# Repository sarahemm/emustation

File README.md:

# emustation
Modular cyberdeck project

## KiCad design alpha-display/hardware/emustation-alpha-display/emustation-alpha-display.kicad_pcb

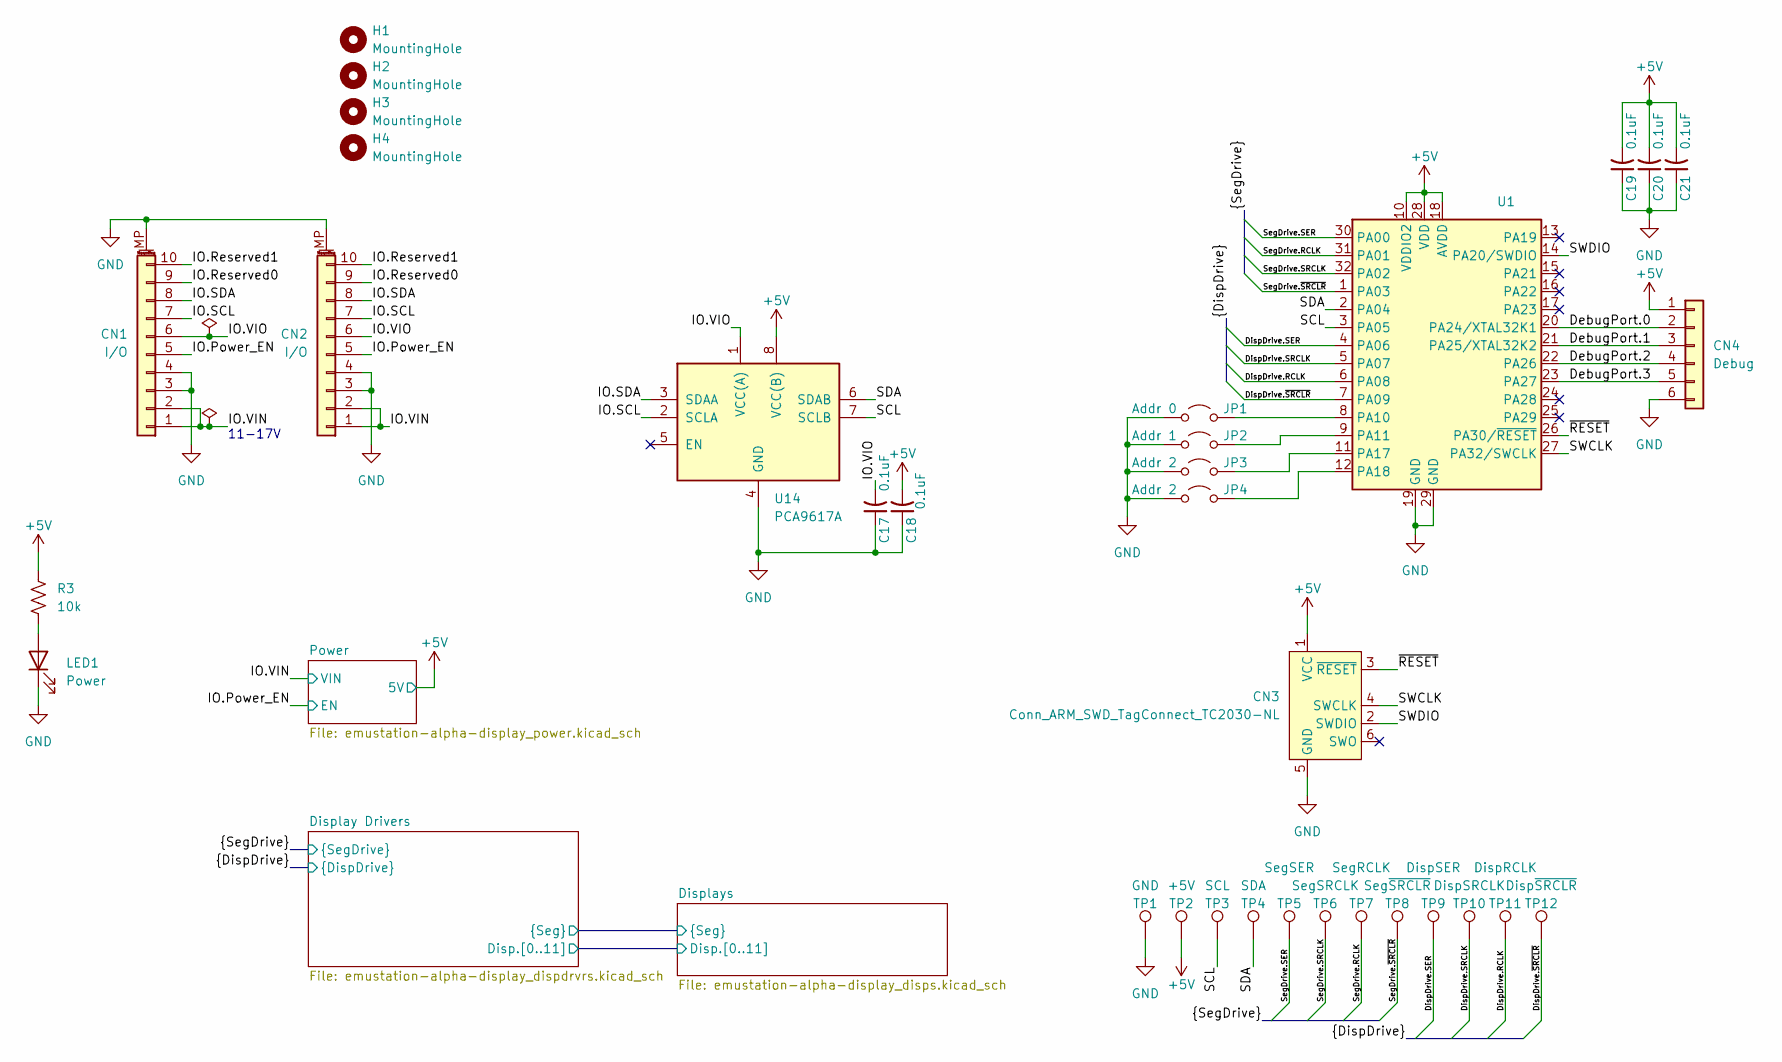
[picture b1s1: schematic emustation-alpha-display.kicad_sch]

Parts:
C17, C18, C19, C20, C21: 0.1uF; C_0603_1608Metric
CN1, CN2: I/O; CF4210FH0R0-05-NH_1x10-1MP_P0.50mm_Horizontal
CN3: Conn_ARM_SWD_TagConnect_TC2030-NL; Tag-Connect_TC2030-IDC-NL_2x03_P1.27mm_Vertical
CN4: Debug; PinHeader_2x03_P1.00mm_Vertical
H1, H2, H3, H4: MountingHole; MountingHole_3.2mm_M3
JP1: Addr 0; SolderJumper-2_P1.3mm_Open_TrianglePad1.0x1.5mm
JP2: Addr 1; SolderJumper-2_P1.3mm_Open_TrianglePad1.0x1.5mm
JP3, JP4: Addr 2; SolderJumper-2_P1.3mm_Open_TrianglePad1.0x1.5mm
LED1: Power; LED_1206_3216Metric
R3: 10k; R_0603_1608Metric
TP1: GND; TestPoint_THTPad_D2.0mm_Drill1.0mm
TP2: +5V; TestPoint_Pad_3.0x3.0mm
TP3: SCL; TestPoint_Pad_2.0x2.0mm
TP4: SDA; TestPoint_Pad_2.0x2.0mm
TP5: SegSER; TestPoint_Pad_2.0x2.0mm
TP6: SegSRCLK; TestPoint_Pad_2.0x2.0mm
TP7: SegRCLK; TestPoint_Pad_2.0x2.0mm
TP8: Seg~{SRCLR}; TestPoint_Pad_2.0x2.0mm
TP9: DispSER; TestPoint_Pad_1.0x1.0mm
TP10: DispSRCLK; TestPoint_Pad_1.0x1.0mm
TP11: DispRCLK; TestPoint_Pad_1.0x1.0mm
TP12: Disp~{SRCLR}; TestPoint_Pad_1.0x1.0mm
U1: TQFP-32_7x7mm_P0.8mm
U14: PCA9617A; TSSOP-8_3x3mm_P0.65mm

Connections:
+5V: C18.2, C19.2, C20.2, C21.2, CN3.1 (VCC), CN4.1, R3.1, TP2.1 (1_1), U1.10 (VDDIO2), U1.18 (AVDD), U1.28 (VDD), U14.8 (VCC(B)); also elsewhere on the board
/DebugPort.0: CN4.2, U1.20 (PA24/XTAL32K1)
/DebugPort.1: CN4.3, U1.21 (PA25/XTAL32K2)
/DebugPort.2: CN4.4, U1.22 (PA26)
/DebugPort.3: CN4.5, U1.23 (PA27)
/DispDrive.RCLK: TP11.1 (1_1), U1.6 (PA08); also elsewhere on the board
/DispDrive.SER: TP9.1 (1_1), U1.4 (PA06); also elsewhere on the board
/DispDrive.SRCLK: TP10.1 (1_1), U1.5 (PA07); also elsewhere on the board
/DispDrive.~SRCLR: TP12.1 (1_1), U1.7 (PA09); also elsewhere on the board
/IO.Power_EN: CN1.5, CN2.5; also elsewhere on the board
/IO.Reserved0: CN1.9, CN2.9
/IO.Reserved1: CN1.10, CN2.10
/IO.SCL: CN1.7, CN2.7, U14.2 (SCLA)
/IO.SDA: CN1.8, CN2.8, U14.3 (SDAA)
/IO.VIN: CN1.1, CN1.2, CN2.1, CN2.2; also elsewhere on the board
/IO.VIO: C17.2, CN1.6, CN2.6, U14.1 (VCC(A))
/SCL: TP3.1 (1_1), U1.3 (PA05), U14.7 (SCLB)
/SDA: TP4.1 (1_1), U1.2 (PA04), U14.6 (SDAB)
/SWCLK: CN3.4 (SWCLK), U1.27 (PA32/SWCLK)
/SWDIO: CN3.2 (SWDIO), U1.14 (PA20/SWDIO)
/SegDrive.RCLK: TP7.1 (1_1), U1.31 (PA01); also elsewhere on the board
/SegDrive.SER: TP5.1 (1_1), U1.30 (PA00); also elsewhere on the board
/SegDrive.SRCLK: TP6.1 (1_1), U1.32 (PA02); also elsewhere on the board
/SegDrive.~SRCLR: TP8.1 (1_1), U1.1 (PA03); also elsewhere on the board
/~RESET: CN3.3 (~RESET), U1.26 (PA30/~RESET)
GND: C17.1, C18.1, C19.1, C20.1, C21.1, CN1.3, CN1.4, CN1.MP (MountPin), CN2.3, CN2.4, CN2.MP (MountPin), CN3.5 (GND), CN4.6, JP1.1 (A), JP2.1 (A), JP3.1 (A), JP4.1 (A), LED1.1 (K), TP1.1 (1_1), U1.19 (GND), U1.29 (GND), U14.4 (GND); also elsewhere on the board
unnamed: JP1.2 (B), U1.8 (PA10)
unnamed: JP2.2 (B), U1.9 (PA11)
unnamed: JP3.2 (B), U1.11 (PA17)
unnamed: JP4.2 (B), U1.12 (PA18)
unnamed: LED1.2 (A), R3.2

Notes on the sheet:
11-17V

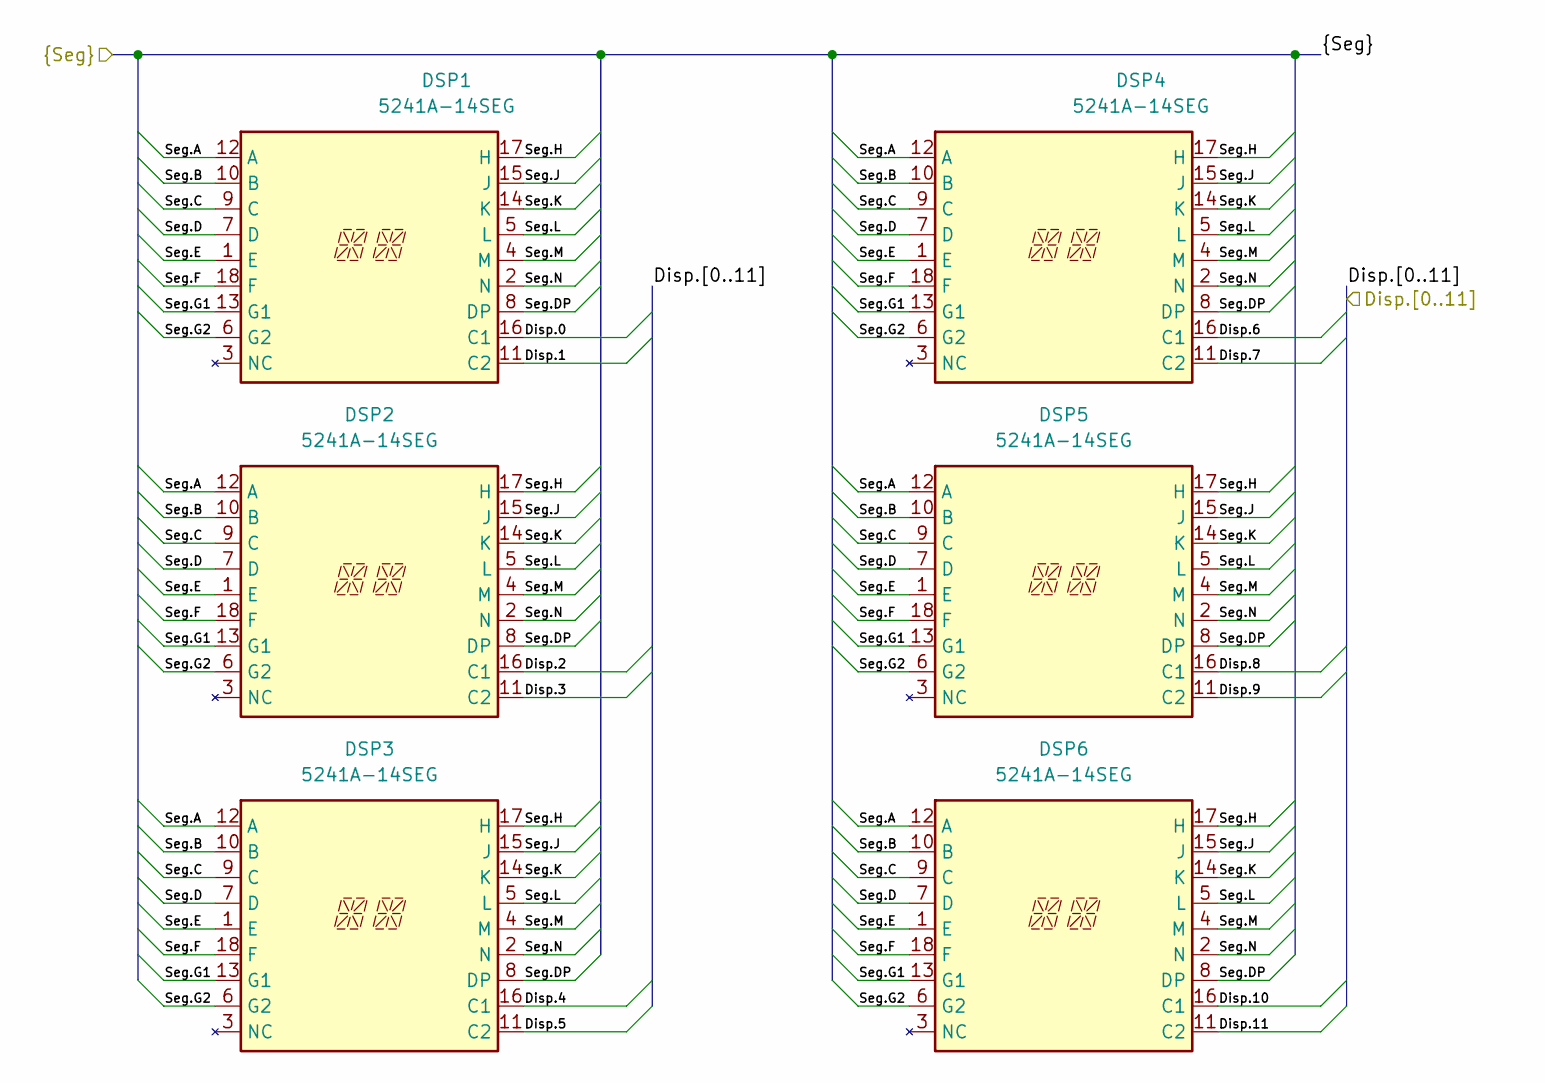
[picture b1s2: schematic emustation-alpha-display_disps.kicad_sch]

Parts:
DSP1, DSP2, DSP3, DSP4, DSP5, DSP6: 5241A-14SEG

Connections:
/Display Drivers/Disp.0: DSP1.16 (C1); also elsewhere on the board
/Display Drivers/Disp.1: DSP1.11 (C2); also elsewhere on the board
/Display Drivers/Disp.2: DSP2.16 (C1); also elsewhere on the board
/Display Drivers/Disp.3: DSP2.11 (C2); also elsewhere on the board
/Display Drivers/Disp.4: DSP3.16 (C1); also elsewhere on the board
/Display Drivers/Disp.5: DSP3.11 (C2); also elsewhere on the board
/Display Drivers/Disp.6: DSP4.16 (C1); also elsewhere on the board
/Display Drivers/Disp.7: DSP4.11 (C2); also elsewhere on the board
/Display Drivers/Disp.8: DSP5.16 (C1); also elsewhere on the board
/Display Drivers/Disp.9: DSP5.11 (C2); also elsewhere on the board
/Display Drivers/Disp.10: DSP6.16 (C1); also elsewhere on the board
/Display Drivers/Disp.11: DSP6.11 (C2); also elsewhere on the board
/Display Drivers/Seg.A: DSP1.12 (A), DSP2.12 (A), DSP3.12 (A), DSP4.12 (A), DSP5.12 (A), DSP6.12 (A); also elsewhere on the board
/Display Drivers/Seg.B: DSP1.10 (B), DSP2.10 (B), DSP3.10 (B), DSP4.10 (B), DSP5.10 (B), DSP6.10 (B); also elsewhere on the board
/Display Drivers/Seg.C: DSP1.9 (C), DSP2.9 (C), DSP3.9 (C), DSP4.9 (C), DSP5.9 (C), DSP6.9 (C); also elsewhere on the board
/Display Drivers/Seg.D: DSP1.7 (D), DSP2.7 (D), DSP3.7 (D), DSP4.7 (D), DSP5.7 (D), DSP6.7 (D); also elsewhere on the board
/Display Drivers/Seg.DP: DSP1.8 (DP), DSP2.8 (DP), DSP3.8 (DP), DSP4.8 (DP), DSP5.8 (DP), DSP6.8 (DP); also elsewhere on the board
/Display Drivers/Seg.E: DSP1.1 (E), DSP2.1 (E), DSP3.1 (E), DSP4.1 (E), DSP5.1 (E), DSP6.1 (E); also elsewhere on the board
/Display Drivers/Seg.F: DSP1.18 (F), DSP2.18 (F), DSP3.18 (F), DSP4.18 (F), DSP5.18 (F), DSP6.18 (F); also elsewhere on the board
/Display Drivers/Seg.G1: DSP1.13 (G1), DSP2.13 (G1), DSP3.13 (G1), DSP4.13 (G1), DSP5.13 (G1), DSP6.13 (G1); also elsewhere on the board
/Display Drivers/Seg.G2: DSP1.6 (G2), DSP2.6 (G2), DSP3.6 (G2), DSP4.6 (G2), DSP5.6 (G2), DSP6.6 (G2); also elsewhere on the board
/Display Drivers/Seg.H: DSP1.17 (H), DSP2.17 (H), DSP3.17 (H), DSP4.17 (H), DSP5.17 (H), DSP6.17 (H); also elsewhere on the board
/Display Drivers/Seg.J: DSP1.15 (J), DSP2.15 (J), DSP3.15 (J), DSP4.15 (J), DSP5.15 (J), DSP6.15 (J); also elsewhere on the board
/Display Drivers/Seg.K: DSP1.14 (K), DSP2.14 (K), DSP3.14 (K), DSP4.14 (K), DSP5.14 (K), DSP6.14 (K); also elsewhere on the board
/Display Drivers/Seg.L: DSP1.5 (L), DSP2.5 (L), DSP3.5 (L), DSP4.5 (L), DSP5.5 (L), DSP6.5 (L); also elsewhere on the board
/Display Drivers/Seg.M: DSP1.4 (M), DSP2.4 (M), DSP3.4 (M), DSP4.4 (M), DSP5.4 (M), DSP6.4 (M); also elsewhere on the board
/Display Drivers/Seg.N: DSP1.2 (N), DSP2.2 (N), DSP3.2 (N), DSP4.2 (N), DSP5.2 (N), DSP6.2 (N); also elsewhere on the board

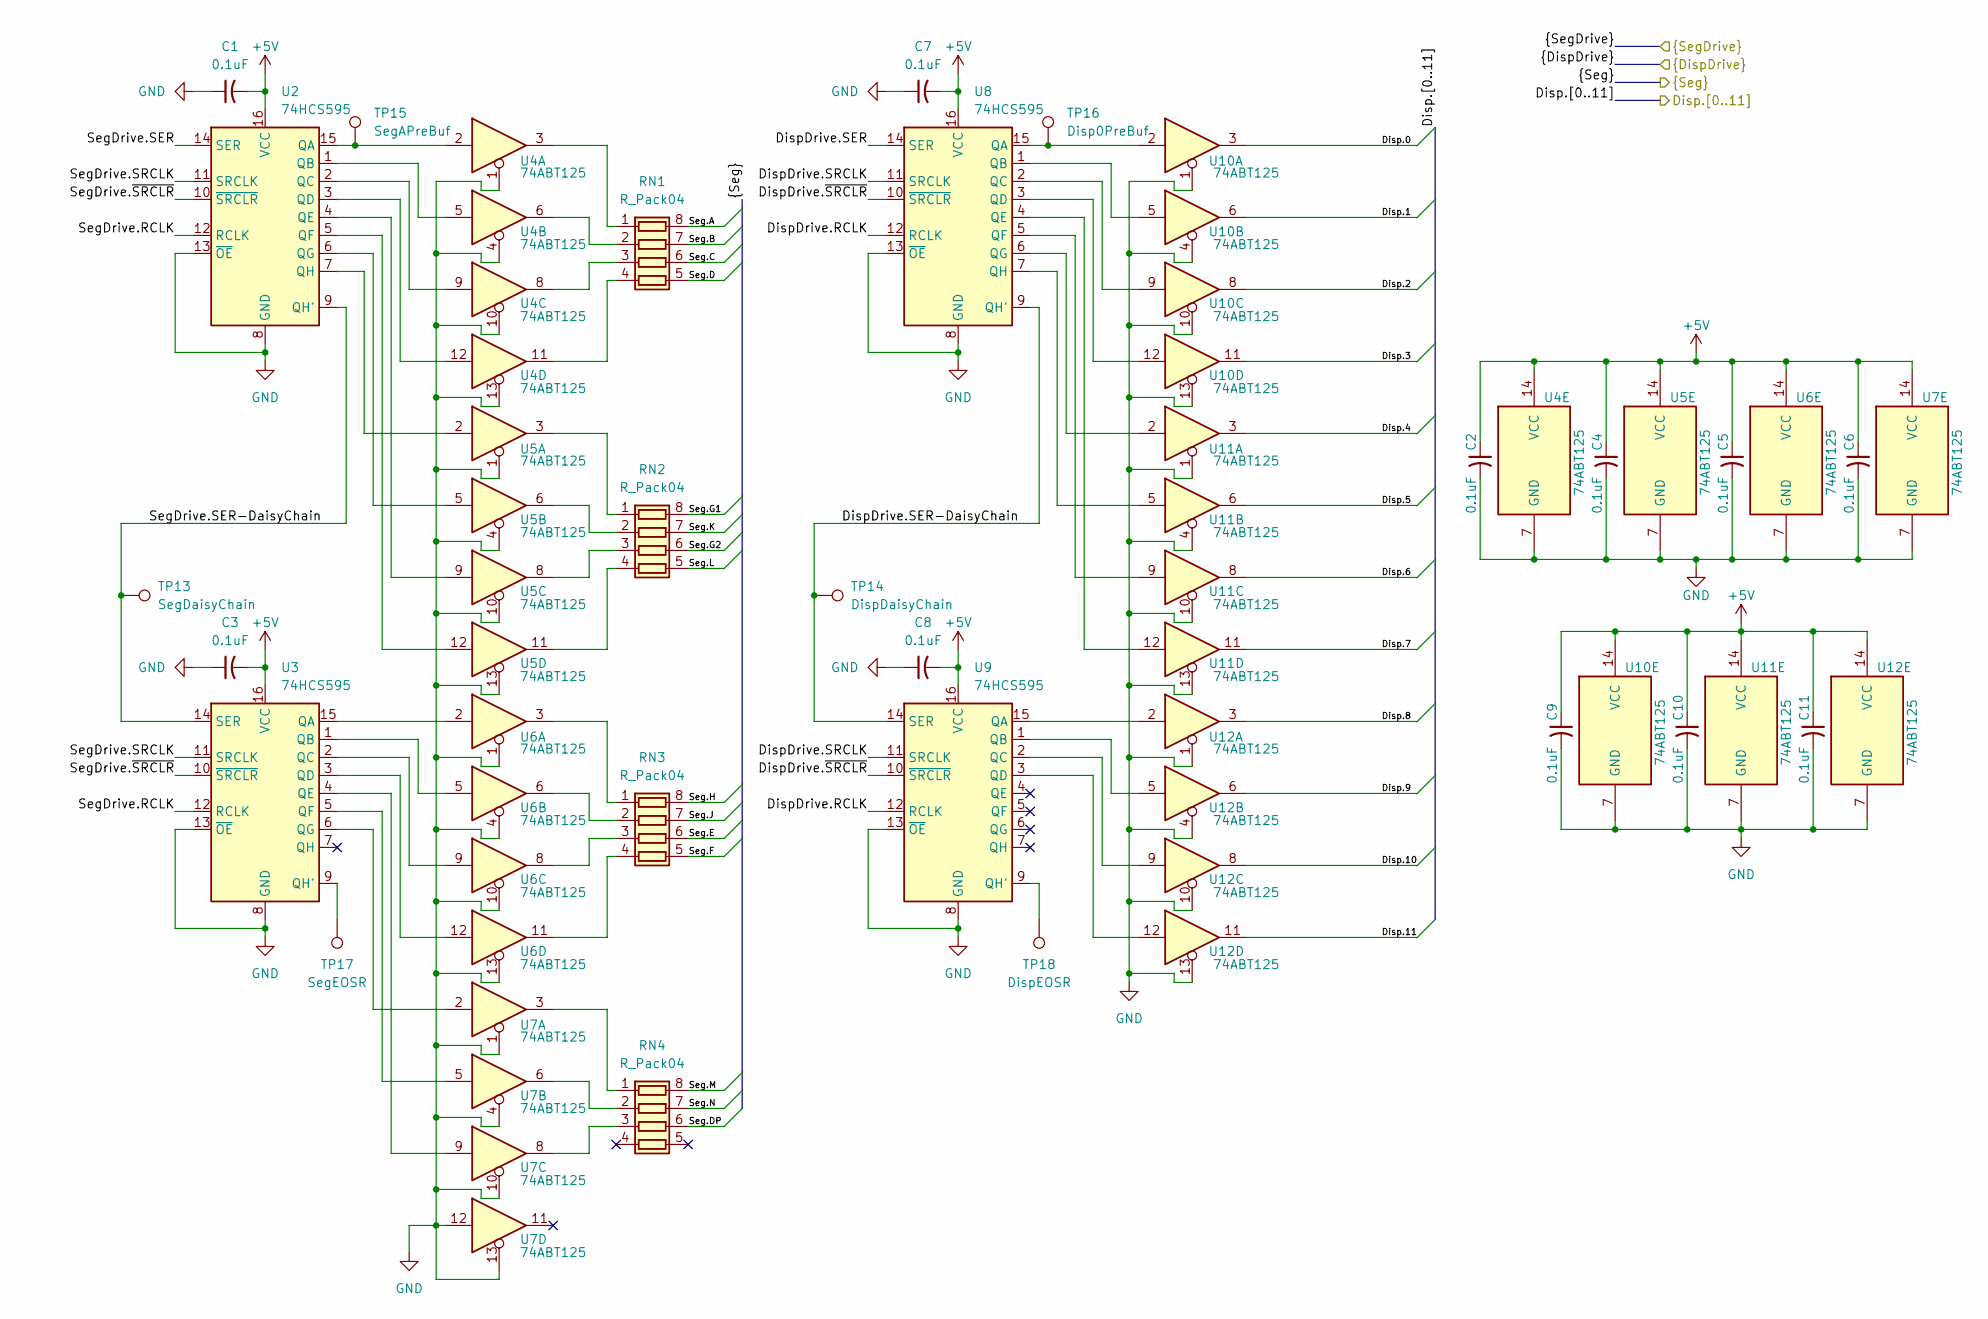
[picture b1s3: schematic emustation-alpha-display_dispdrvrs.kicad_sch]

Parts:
C1, C2, C3, C4, C5, C6, C7, C8, C9, C10, C11: 0.1uF; C_0603_1608Metric
RN1, RN2, RN3, RN4: R_Pack04; R_Array_Convex_4x0603
TP13: SegDaisyChain; TestPoint_Pad_2.0x2.0mm
TP14: DispDaisyChain; TestPoint_Pad_2.0x2.0mm
TP15: SegAPreBuf; TestPoint_Pad_2.0x2.0mm
TP16: Disp0PreBuf; TestPoint_Pad_2.0x2.0mm
TP17: SegEOSR; TestPoint_Pad_2.0x2.0mm
TP18: DispEOSR; TestPoint_Pad_2.0x2.0mm
U2, U3, U8, U9: 74HCS595; TSSOP-16_4.4x5mm_P0.65mm
U4, U5, U6, U7, U10, U11, U12: 74ABT125; TSSOP-14_4.4x5mm_P0.65mm

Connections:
+5V: C1.2, C2.1, C3.2, C4.1, C5.1, C6.1, C7.2, C8.2, C9.1, C10.1, C11.1, U2.16 (VCC), U3.16 (VCC), U4.14 (VCC), U5.14 (VCC), U6.14 (VCC), U7.14 (VCC), U8.16 (VCC), U9.16 (VCC), U10.14 (VCC), U11.14 (VCC), U12.14 (VCC); also elsewhere on the board
/DispDrive.RCLK: U8.12 (RCLK), U9.12 (RCLK); also elsewhere on the board
/DispDrive.SER: U8.14 (SER); also elsewhere on the board
/DispDrive.SRCLK: U8.11 (SRCLK), U9.11 (SRCLK); also elsewhere on the board
/DispDrive.~SRCLR: U8.10 (~SRCLR), U9.10 (~SRCLR); also elsewhere on the board
/Display Drivers/Disp.0: U10.3; also elsewhere on the board
/Display Drivers/Disp.1: U10.6; also elsewhere on the board
/Display Drivers/Disp.2: U10.8; also elsewhere on the board
/Display Drivers/Disp.3: U10.11; also elsewhere on the board
/Display Drivers/Disp.4: U11.3; also elsewhere on the board
/Display Drivers/Disp.5: U11.6; also elsewhere on the board
/Display Drivers/Disp.6: U11.8; also elsewhere on the board
/Display Drivers/Disp.7: U11.11; also elsewhere on the board
/Display Drivers/Disp.8: U12.3; also elsewhere on the board
/Display Drivers/Disp.9: U12.6; also elsewhere on the board
/Display Drivers/Disp.10: U12.8; also elsewhere on the board
/Display Drivers/Disp.11: U12.11; also elsewhere on the board
/Display Drivers/DispDrive.SER-DaisyChain: TP14.1 (1_1), U8.9 (QH'), U9.14 (SER)
/Display Drivers/Seg.A: RN1.8 (R1.2); also elsewhere on the board
/Display Drivers/Seg.B: RN1.7 (R2.2); also elsewhere on the board
/Display Drivers/Seg.C: RN1.6 (R3.2); also elsewhere on the board
/Display Drivers/Seg.D: RN1.5 (R4.2); also elsewhere on the board
/Display Drivers/Seg.DP: RN4.6 (R3.2); also elsewhere on the board
/Display Drivers/Seg.E: RN3.6 (R3.2); also elsewhere on the board
/Display Drivers/Seg.F: RN3.5 (R4.2); also elsewhere on the board
/Display Drivers/Seg.G1: RN2.8 (R1.2); also elsewhere on the board
/Display Drivers/Seg.G2: RN2.6 (R3.2); also elsewhere on the board
/Display Drivers/Seg.H: RN3.8 (R1.2); also elsewhere on the board
/Display Drivers/Seg.J: RN3.7 (R2.2); also elsewhere on the board
/Display Drivers/Seg.K: RN2.7 (R2.2); also elsewhere on the board
/Display Drivers/Seg.L: RN2.5 (R4.2); also elsewhere on the board
/Display Drivers/Seg.M: RN4.8 (R1.2); also elsewhere on the board
/Display Drivers/Seg.N: RN4.7 (R2.2); also elsewhere on the board
/Display Drivers/SegDrive.SER-DaisyChain: TP13.1 (1_1), U2.9 (QH'), U3.14 (SER)
/SegDrive.RCLK: U2.12 (RCLK), U3.12 (RCLK); also elsewhere on the board
/SegDrive.SER: U2.14 (SER); also elsewhere on the board
/SegDrive.SRCLK: U2.11 (SRCLK), U3.11 (SRCLK); also elsewhere on the board
/SegDrive.~SRCLR: U2.10 (~SRCLR), U3.10 (~SRCLR); also elsewhere on the board
GND: C1.1, C2.2, C3.1, C4.2, C5.2, C6.2, C7.1, C8.1, C9.2, C10.2, C11.2, U2.8 (GND), U2.13 (~OE), U3.8 (GND), U3.13 (~OE), U4.1, U4.4, U4.7 (GND), U4.10, U4.13, U5.1, U5.4, U5.7 (GND), U5.10, U5.13, U6.1, U6.4, U6.7 (GND), U6.10, U6.13, U7.1, U7.4, U7.7 (GND), U7.10, U7.12, U7.13, U8.8 (GND), U8.13 (~OE), U9.8 (GND), U9.13 (~OE), U10.1, U10.4, U10.7 (GND), U10.10, U10.13, U11.1, U11.4, U11.7 (GND), U11.10, U11.13, U12.1, U12.4, U12.7 (GND), U12.10, U12.13; also elsewhere on the board
unnamed: RN1.1 (R1.1), U4.3
unnamed: RN1.2 (R2.1), U4.6
unnamed: RN1.3 (R3.1), U4.8
unnamed: RN1.4 (R4.1), U4.11
unnamed: RN2.1 (R1.1), U5.3
unnamed: RN2.2 (R2.1), U5.6
unnamed: RN2.3 (R3.1), U5.8
unnamed: RN2.4 (R4.1), U5.11
unnamed: RN3.1 (R1.1), U6.3
unnamed: RN3.2 (R2.1), U6.6
unnamed: RN3.3 (R3.1), U6.8
unnamed: RN3.4 (R4.1), U6.11
unnamed: RN4.1 (R1.1), U7.3
unnamed: RN4.2 (R2.1), U7.6
unnamed: RN4.3 (R3.1), U7.8
unnamed: TP15.1 (1_1), U2.15 (QA), U4.2
unnamed: U2.1 (QB), U4.5
unnamed: U2.2 (QC), U4.9
unnamed: U2.3 (QD), U4.12
unnamed: U2.4 (QE), U5.9
unnamed: U2.5 (QF), U5.12
unnamed: U2.6 (QG), U5.5
unnamed: U2.7 (QH), U5.2
unnamed: U3.15 (QA), U6.2
unnamed: U3.1 (QB), U6.5
unnamed: U3.2 (QC), U6.9
unnamed: U3.3 (QD), U6.12
unnamed: U3.4 (QE), U7.9
unnamed: U3.5 (QF), U7.5
unnamed: U3.6 (QG), U7.2
unnamed: TP17.1 (1_1), U3.9 (QH')
unnamed: TP16.1 (1_1), U8.15 (QA), U10.2
unnamed: U8.1 (QB), U10.5
unnamed: U8.2 (QC), U10.9
unnamed: U8.3 (QD), U10.12
unnamed: U8.4 (QE), U11.12
unnamed: U8.5 (QF), U11.9
unnamed: U8.6 (QG), U11.2
unnamed: U8.7 (QH), U11.5
unnamed: U9.15 (QA), U12.2
unnamed: U9.1 (QB), U12.5
unnamed: U9.2 (QC), U12.9
unnamed: U9.3 (QD), U12.12
unnamed: TP18.1 (1_1), U9.9 (QH')

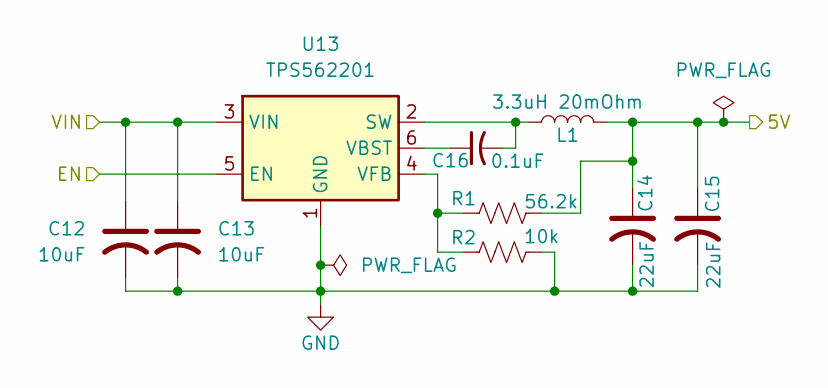
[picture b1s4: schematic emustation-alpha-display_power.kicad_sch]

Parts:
C12, C13: 10uF; C_0805_2012Metric
C14, C15: 22uF; C_0603_1608Metric
C16: 0.1uF; C_0603_1608Metric
L1: 3.3uH 20mOhm; L_APV_ANR8040
R1: 56.2k; R_0603_1608Metric
R2: 10k; R_0603_1608Metric
U13: TPS562201; SOT-563

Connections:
+5V: C14.1, C15.1, L1.2, R1.2; also elsewhere on the board
/IO.Power_EN: U13.5 (EN); also elsewhere on the board
/IO.VIN: C12.1, C13.1, U13.3 (VIN); also elsewhere on the board
GND: C12.2, C13.2, C14.2, C15.2, R2.2, U13.1 (GND); also elsewhere on the board
unnamed: C16.2, L1.1, U13.2 (SW)
unnamed: C16.1, U13.6 (VBST)
unnamed: R1.1, R2.1, U13.4 (VFB)

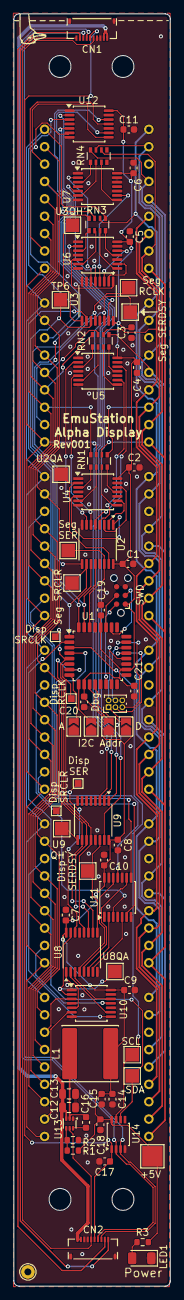
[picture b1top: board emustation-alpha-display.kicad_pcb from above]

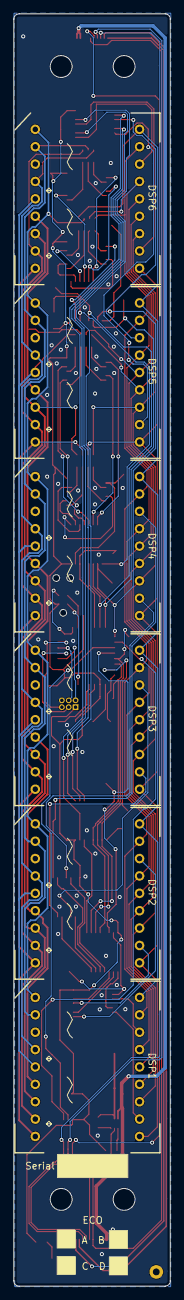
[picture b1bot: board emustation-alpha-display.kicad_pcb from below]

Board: 2 copper layers, 22.9 x 186.0 mm, 80 parts (6 on the bottom side), 107 nets.
